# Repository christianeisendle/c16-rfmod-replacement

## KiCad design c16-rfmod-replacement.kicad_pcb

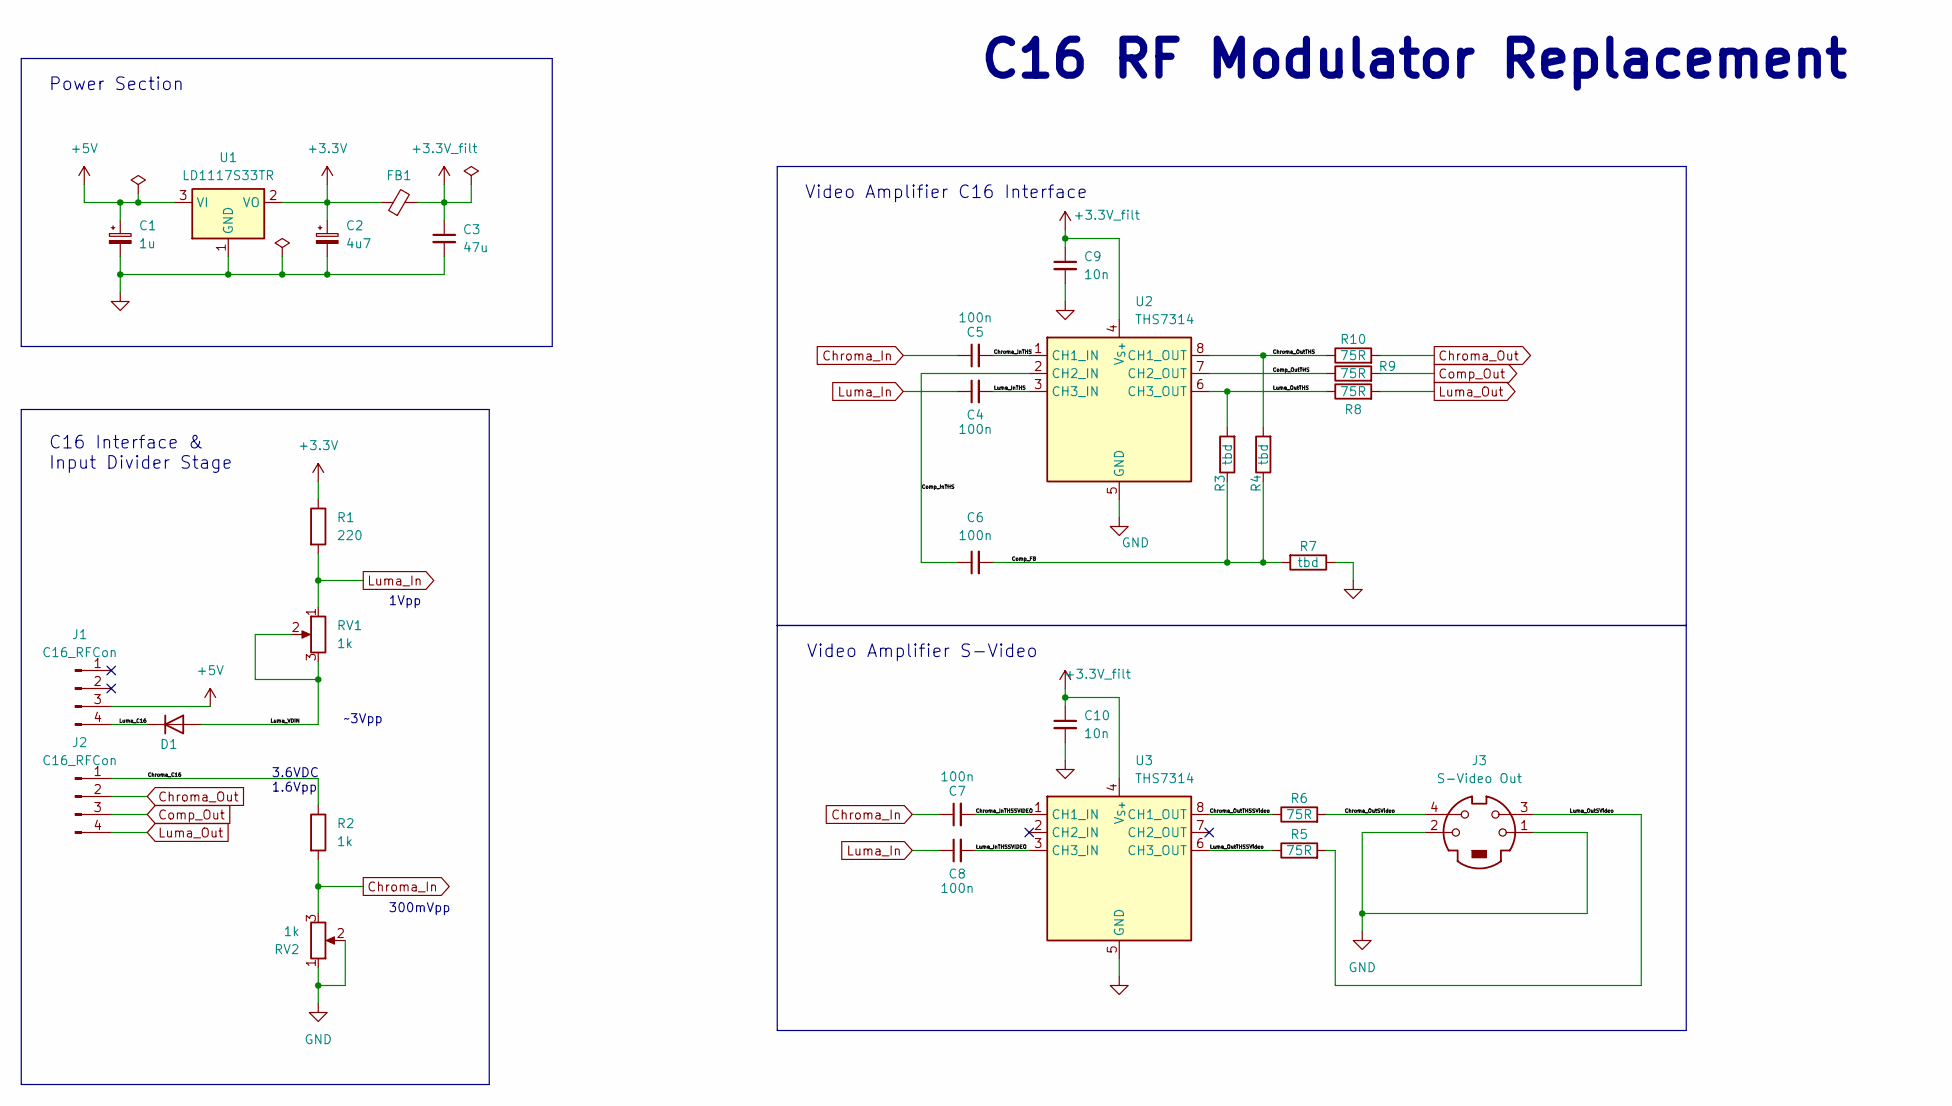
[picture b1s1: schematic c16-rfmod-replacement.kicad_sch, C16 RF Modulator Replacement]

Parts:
C1: 1u; C_0603_1608Metric
C2: 4u7; C_1206_3216Metric
C3: 47u; C_1206_3216Metric
C4, C5, C6, C7, C8: 100n; C_0603_1608Metric
C9, C10: 10n; C_0603_1608Metric
D1: 1N4148WT; D_MiniMELF
FB1: L_0603_1608Metric
J1, J2: C16_RFCon; PinHeader_1x04_P2.54mm_Vertical
J3: S-Video Out; MD2-40ST-SMT
R1: 220; R_0603_1608Metric
R2: 1k; R_0603_1608Metric
R3, R4, R7: tbd; R_0603_1608Metric
R5, R6, R8, R9, R10: 75R; R_0603_1608Metric
RV1, RV2: 1k; Potentiometer_Vishay_TS53YL_Vertical
U1: LD1117S33TR; SOT-223-3_TabPin2
U2, U3: THS7314; SOIC-8_3.9x4.9mm_P1.27mm

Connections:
+3.3V: C2.1, FB1.1, R1.1, U1.2 (VO)
+3.3V_filt: C3.1, C9.1, C10.1, FB1.2, U2.4 (V_{S+}), U3.4 (V_{S+})
+5V: C1.1, J1.3, U1.3 (VI)
/Chroma_C16: J2.1, R2.1
/Chroma_InTHS: C5.2, U2.1 (CH1_IN)
/Chroma_InTHSSVIDEO: C7.2, U3.1 (CH1_IN)
/Chroma_OutSVideo: J3.4, R6.2
/Chroma_OutTHS: R4.2, R10.1, U2.8 (CH1_OUT)
/Chroma_OutTHSSVideo: R6.1, U3.8 (CH1_OUT)
/Comp_FB: C6.2, R3.1, R4.1, R7.2
/Comp_InTHS: C6.1, U2.2 (CH2_IN)
/Comp_OutTHS: R9.1, U2.7 (CH2_OUT)
/Luma_C16: D1.1 (K), J1.4
/Luma_InTHS: C4.2, U2.3 (CH3_IN)
/Luma_InTHSSVIDEO: C8.2, U3.3 (CH3_IN)
/Luma_OutSVideo: J3.3, R5.2
/Luma_OutTHS: R3.2, R8.1, U2.6 (CH3_OUT)
/Luma_OutTHSSVideo: R5.1, U3.6 (CH3_OUT)
/Luma_VDIN: D1.2 (A), RV1.2, RV1.3
Chroma_In: C5.1, C7.1, R2.2, RV2.3
Chroma_Out: J2.2, R10.2
Comp_Out: J2.3, R9.2
GND: C1.2, C2.2, C3.2, C9.2, C10.2, J3.1, J3.2, R7.1, RV2.1, RV2.2, U1.1 (GND), U2.5 (GND), U3.5 (GND)
Luma_In: C4.1, C8.1, R1.2, RV1.1
Luma_Out: J2.4, R8.2

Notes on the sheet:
C16 RF Modulator Replacement
Video Amplifier S-Video
Video Amplifier C16 Interface
C16 Interface & Input Divider Stage
Power Section
3.6VDC 1.6Vpp
1Vpp
~3Vpp
300mVpp

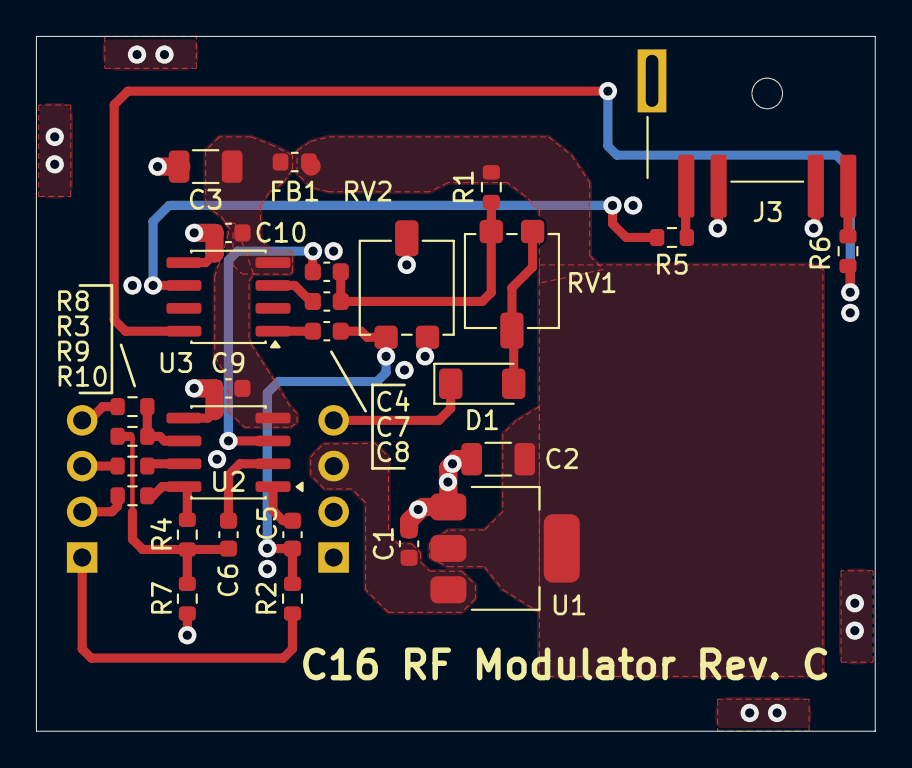
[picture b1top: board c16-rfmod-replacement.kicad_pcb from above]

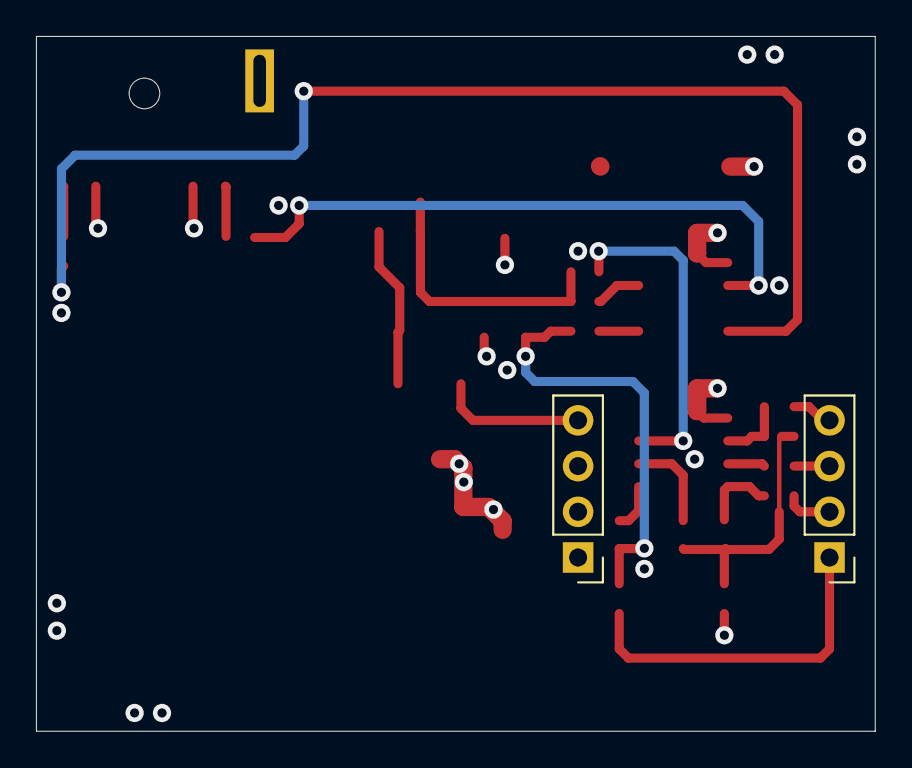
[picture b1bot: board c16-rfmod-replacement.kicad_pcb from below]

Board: 4 copper layers, 46.6 x 38.6 mm, 30 parts (2 on the bottom side), 25 nets.

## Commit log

2026-03-30 Add Kicad design files
2026-04-01 Change value of R8 and RV1
2026-04-18 C16 RF modulator replacement Rev. B
2026-04-19 Rev. C - Dual Output Amplifier
